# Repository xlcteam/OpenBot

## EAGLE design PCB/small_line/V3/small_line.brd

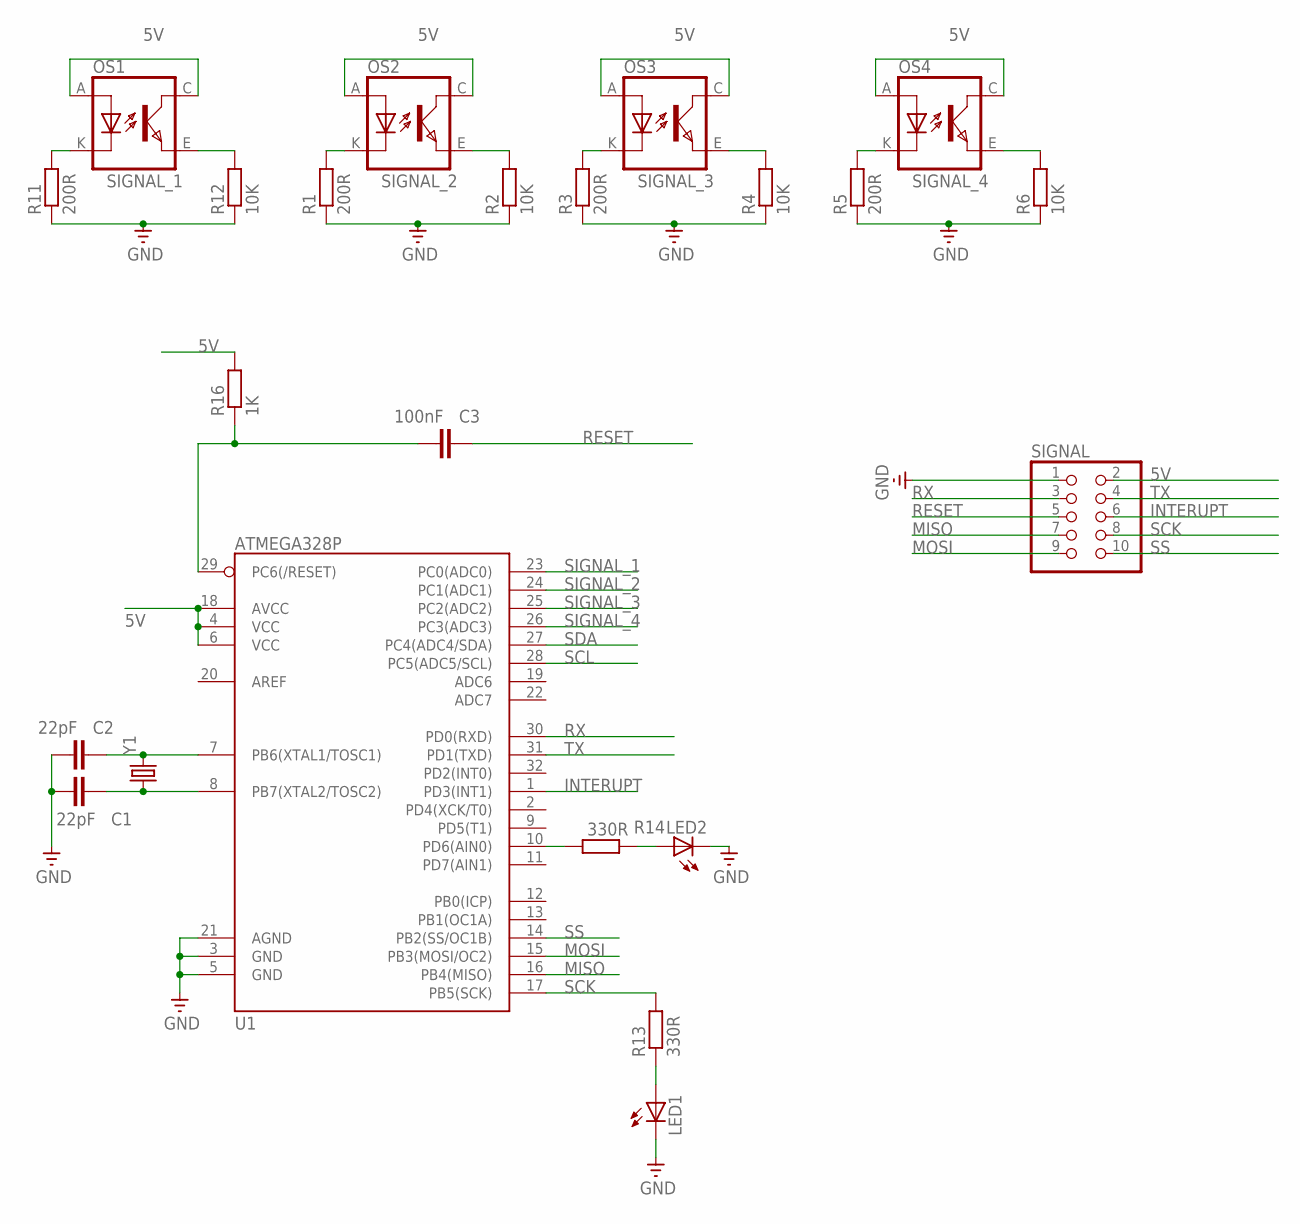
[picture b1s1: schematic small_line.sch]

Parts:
C1, C2: 22pF; C0603
C3: 100nF; C0603
LED1, LED2: LEDCHIPLED_0603; CHIPLED_0603
OS1, OS2, OS3, OS4: TCRT5000
R1, R3, R5, R11: 200R; R0603
R2, R4, R6, R12: 10K; R0603
R13, R14: 330R; R0603
R16: 1K; R0603
SIGNAL: PINHD-2X5; 2X05
U1: ATMEGA328P; TQFP32-08
Y1: CRYSTALHC49US; HC49US

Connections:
5V: OS1.A (ANODE), OS1.C (COLLECTOR), OS2.A (ANODE), OS2.C (COLLECTOR), OS3.A (ANODE), OS3.C (COLLECTOR), OS4.A (ANODE), OS4.C (COLLECTOR), R16.2, SIGNAL.2, U1.4 (VCC), U1.6 (VCC), U1.18 (AVCC); also elsewhere on the board
GND: C1.1, C2.1, LED1.C, LED2.C, R1.1, R2.1, R3.1, R4.1, R5.1, R6.1, R11.1, R12.1, SIGNAL.1, U1.3 (GND), U1.5 (GND), U1.21 (AGND); also elsewhere on the board
INTERUPT: SIGNAL.6, U1.1 (PD3(INT1))
MISO: SIGNAL.7, U1.16 (PB4(MISO))
MOSI: SIGNAL.9, U1.15 (PB3(MOSI/OC2))
unnamed: OS2.K (CATHODE), R1.2
unnamed: OS3.K (CATHODE), R3.2
unnamed: OS4.K (CATHODE), R5.2
unnamed: OS1.K (CATHODE), R11.2
unnamed: C2.2, U1.7 (PB6(XTAL1/TOSC1)), Y1.2
unnamed: C1.2, U1.8 (PB7(XTAL2/TOSC2)), Y1.1
unnamed: C3.1, R16.1, U1.29 (PC6(/RESET))
unnamed: LED1.A, R13.1
unnamed: LED2.A, R14.1
unnamed: R14.2, U1.10 (PD6(AIN0))
RESET: C3.2, SIGNAL.5
RX: SIGNAL.3, U1.30 (PD0(RXD))
SCK: R13.2, SIGNAL.8, U1.17 (PB5(SCK))
SCL: U1.28 (PC5(ADC5/SCL))
SDA: U1.27 (PC4(ADC4/SDA))
SIGNAL_1: OS1.E (EMITTER), R12.2, U1.23 (PC0(ADC0))
SIGNAL_2: OS2.E (EMITTER), R2.2, U1.24 (PC1(ADC1))
SIGNAL_3: OS3.E (EMITTER), R4.2, U1.25 (PC2(ADC2))
SIGNAL_4: OS4.E (EMITTER), R6.2, U1.26 (PC3(ADC3))
SS: SIGNAL.10, U1.14 (PB2(SS/OC1B))
TX: SIGNAL.4, U1.31 (PD1(TXD))

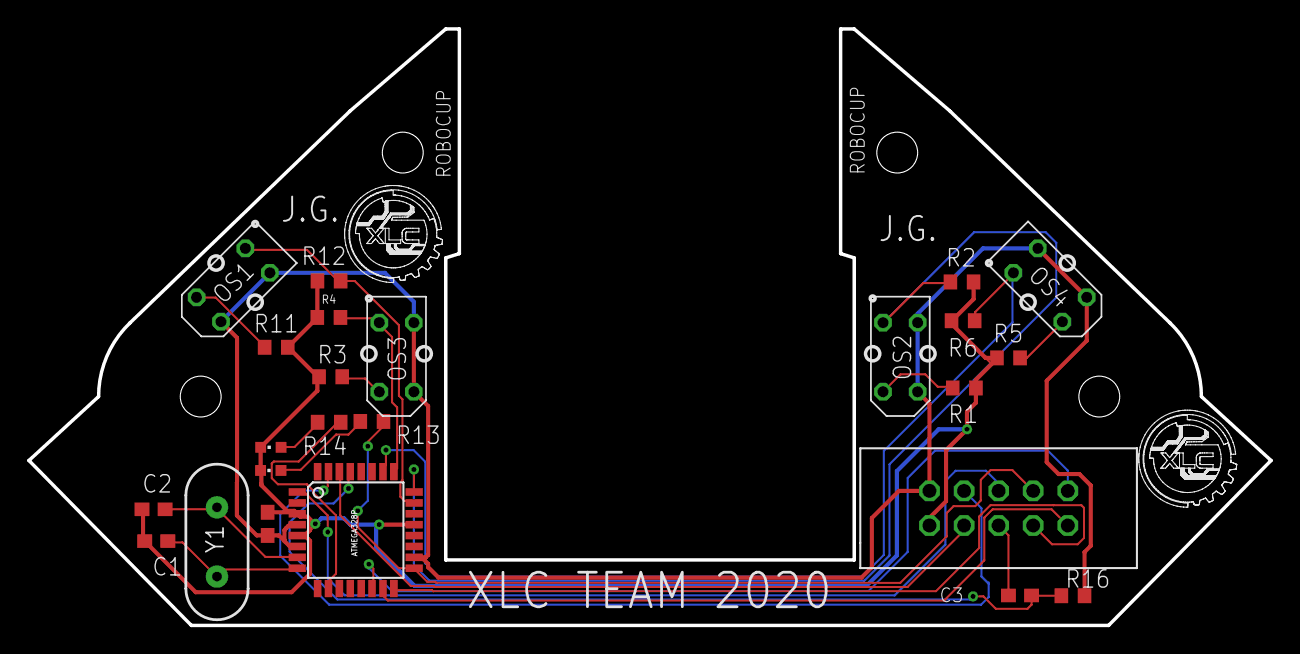
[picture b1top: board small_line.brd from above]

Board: 2 copper layers, 91.2 x 43.8 mm, 24 parts (0 on the bottom side), 24 nets.

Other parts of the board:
C4: C0603

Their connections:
5V: C4.2; also elsewhere on the board
GND: C4.1; also elsewhere on the board

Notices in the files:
parts and their libraries:
SparkFun-DigitalIC: Licensing: CC v3.0 Share-Alike You are welcome to use this library for commercial purposes.
